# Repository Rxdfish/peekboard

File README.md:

Repo for peekboard a small desk display, showing some infos about this and that 

# peekboard

This is a practical and useful table display. Its meant to create a info dashboard to display all sorts of stuff. It could show your notifications and files or simply the time and date. 
This project is WOP so expect changes and updates in future!

# What is this

Peekboard is another project, made for the [Half life](https://halflife.hackclub.com) by Hackclub YSWS program. The motivation for this project was to build a display. Since bigger displays cost more money, this 4" TFT screen was everything that fit into the tight budget. Even though the limitations, I think it worked out quite nicely and im really excited to test it out myself.

The Board features as probably suspected a Microcontroller, display, some buttons and rotary encoders and a USB-C receptacle. The whole board fits into one hand!

# Project status

The project is as already said a WOP and there will come more polished versions of the project. Also in work is an enclosure for the display, that can be 3D printed.  

# Detailed description

More detailed description coming soon. For now refer to the images and the #What is this chapter.
-features
-controls
-menus
-settings

# Motivation

There was no deeper motivation than to differentiate my skills more and test some new components. Half life gave the display topic and I went with it happily.

# Project journaling

Via the [Half life](https://halflife.hackclub.com) by Hackclub programm, several Journal entries have been made either in timelaps form or as written entry to track the project, that describe the project further. Right now they arent public, but either they will, or some screenshots will be added to the repo

# Assembly

The assembly should be quite beginnerfriendly. All components can be handsoldered onto a PCB that can be ordered by a manufacturer like [JLPCB](https://jlcpcb.com/). Maybe a video tutorial will be added later (if the repo is seen, but prob. not). 

# Schematic and components

The board is powered by the ESP32-S3-WROOM-1-N16R8. It provides some power and data for flashing and firmware. The board also features another USB-C receptacle for main power of the TFT screen. This display is a 4" st7796 SPI TFT 480x320 screen, that is fairly big for its price. For navigation, setup and use, there are several buttons and rotary encoders.
If you want to see the schematic in more detail, have a look into the images folder!

# PCB

The PCB is a simple 2 layer PCB with another silkscreen layer for cosmetic and organisational purposes. The board also has a standart GND pour and features routing on the front and backside.

closeup

# Firmware

There is no official firmware yet but there is some test software inside the repo and the basic firmware for the screen. More will follow soon.

**!Short disclaimer for half life!**

There is no finished .ino or .py file in the repo but there are some test script in other formats for the screen. The actual finished firmware will be created in the build week.

# BOM
There are two BOM files inside the repo. One is the entire parts list with all passives and main components. Its stored in BOM2. The other is the list below or saved in [BOM.csv](BOM.csv). THis is the funded parts list for the YSWS program by hackclub. If you build the project, you will need BOM2. 

embedded (HL): 
PEEKBOARD – bill of materials
!! The PCB manufacturing was excluded from the list unfortunately because of over budgeting :(
				
| Part | Qty | Unit-Price | total | Shop | Link |
| --- | --- | --- | --- | --- | --- |
| 4" st7796 SPI TFT 480x320 | 1 | $20.93 | $20.93 | AliExpress | [Link](https://de.aliexpress.com/item/1005007609041421.html?spm=a2g0o.cart.0.0.502038dawLfZEM&mp=1&gatewayAdapt=glo2deu) |
| USBLC6-2SC6 | 1 | $1.72 | $1.72 | AliExpress | [Link](https://de.aliexpress.com/item/1005007348100430.html?spm=a2g0o.cart.0.0.502038dawLfZEM&mp=1&gatewayAdapt=glo2deu) |
| AP1221K-3.3 TRG1 | 1 | $2.36 | $2.36 | AliExpress | [Link](https://de.aliexpress.com/item/1005005807114594.html?spm=a2g0o.cart.0.0.502038daN9aA73&mp=1&gatewayAdapt=glo2deu) |
| AO3401A | 1 | $2.09 | $2.09 | AliExpress | [Link](https://www.aliexpress.com/item/1005006220143887.html?spm=a2g0o.cart.0.0.44c538daCDAQGZ&mp=1) |
| Alps EC11E155244G1 | 1 | $1.27 | $1.27 | AliExpress | [Link](https://de.aliexpress.com/item/1005007644083514.html?spm=a2g0o.cart.0.0.502038daN9aA73&mp=1&gatewayAdapt=glo2deu) |
| 1206 PTC self recovery fuse 0.75A | 1 | $1.93 | $1.93 | AliExpress | [Link](https://de.aliexpress.com/item/1005005750933997.html?spm=a2g0o.cart.0.0.44c538daCDAQGZ&mp=1&gatewayAdapt=glo2deu) |
| (PCB manufacturing) | 5 | $8.6 | $8.6 | JLPCB | [Link](https://cart.jlcpcb.com/de/quote?stencilLayer=2&stencilWidth=100&stencilLength=100&stencilCounts=5&plateType=1&spm=Jlcpcb.Homepage.1010) |
| **Total** | **$28.93** | | Shipping: free | (Shipping for PCB: $8.99) | |

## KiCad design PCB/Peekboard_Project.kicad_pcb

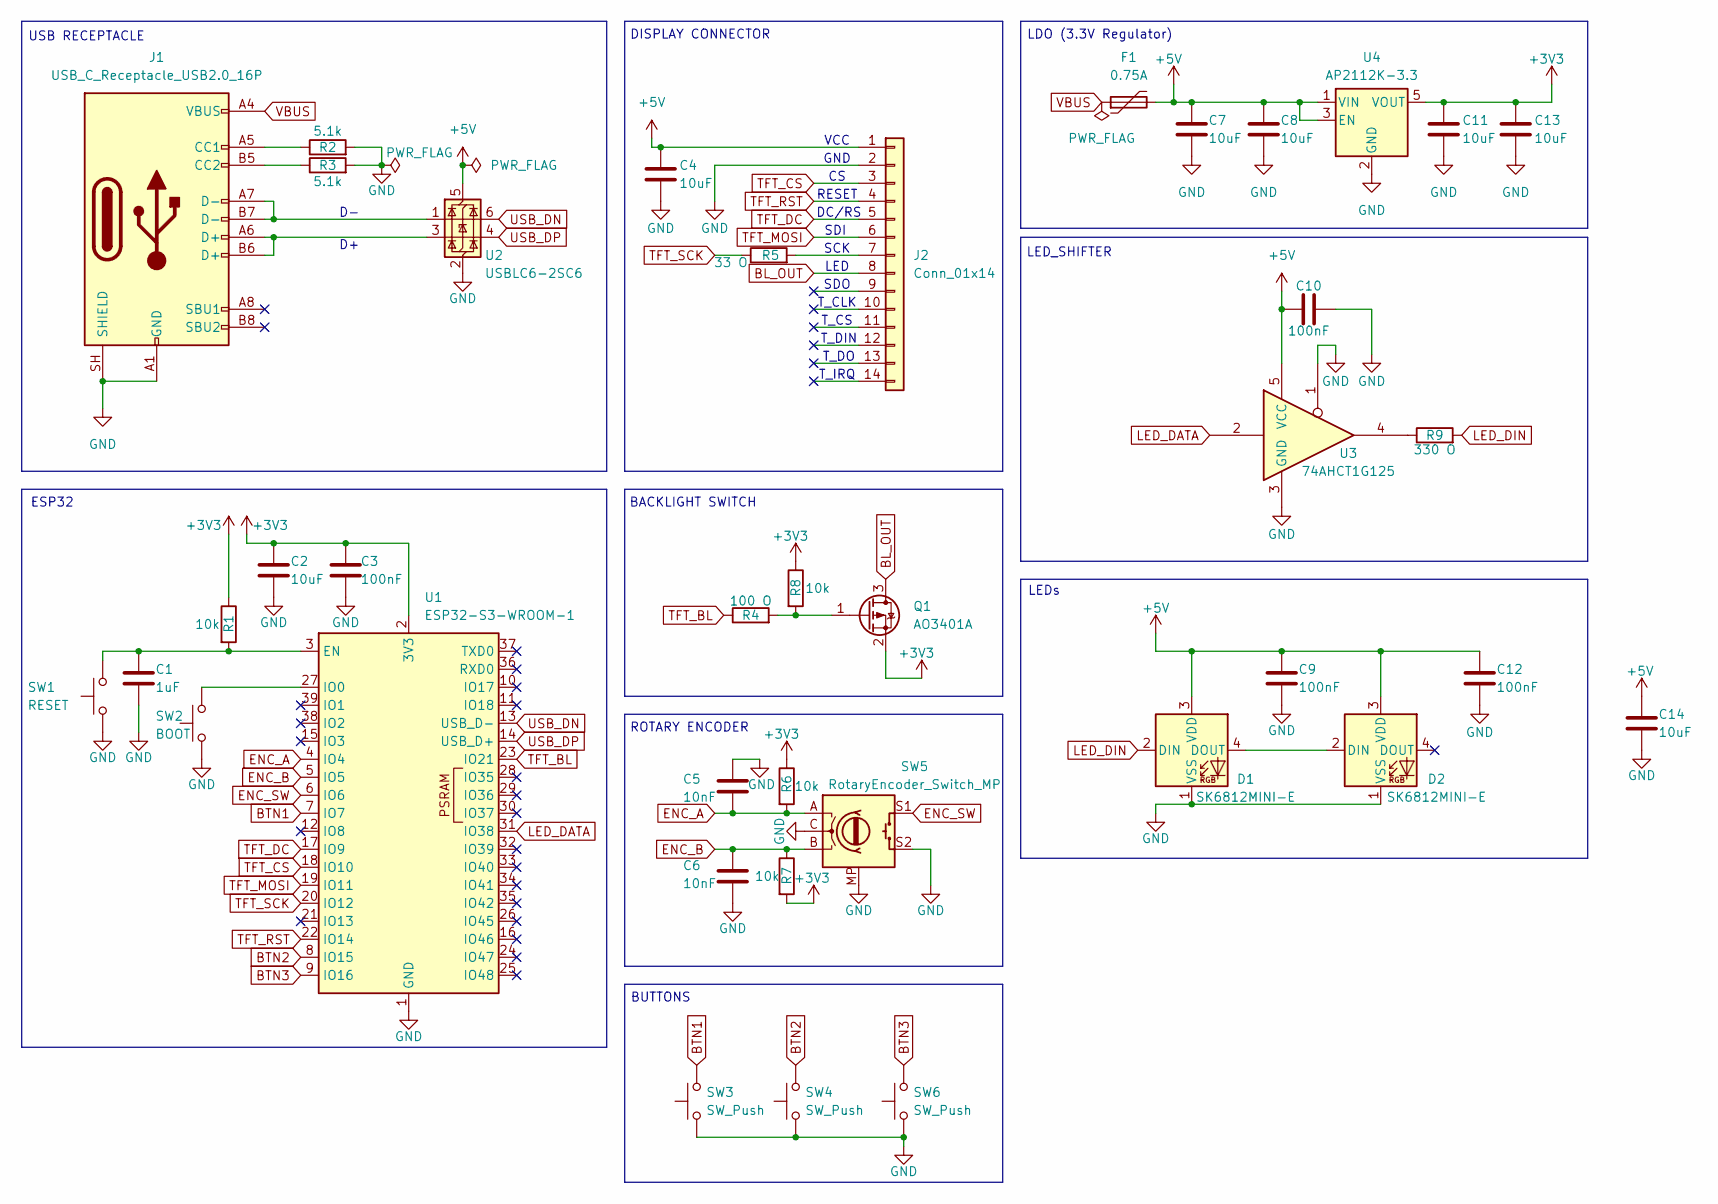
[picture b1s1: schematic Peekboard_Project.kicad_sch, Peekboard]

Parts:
C1: 1uF; C_0805_2012Metric_Pad1.18x1.45mm_HandSolder
C2, C4, C7, C8, C11, C13, C14: 10uF; C_0805_2012Metric_Pad1.18x1.45mm_HandSolder
C3, C9, C10, C12: 100nF; C_0805_2012Metric_Pad1.18x1.45mm_HandSolder
C5, C6: 10nF; C_0805_2012Metric_Pad1.18x1.45mm_HandSolder
D1, D2: SK6812MINI-E; LED_SK6812MINI-E_3.2x2.8mm_P1.5mm_ReverseMount
F1: 0.75A; Fuse_1206_3216Metric_Pad1.42x1.75mm_HandSolder
J1: USB_C_Receptacle_USB2.0_16P; USB_C_Receptacle_HRO_TYPE-C-31-M-12
J2: Conn_01x14; MSP4030_Module
Q1: AO3401A; SOT-23
R1, R6, R7, R8: 10k; R_0805_2012Metric_Pad1.20x1.40mm_HandSolder
R2, R3: 5.1k; R_0805_2012Metric_Pad1.20x1.40mm_HandSolder
R4: 100 O; R_0805_2012Metric_Pad1.20x1.40mm_HandSolder
R5: 33 O; R_0805_2012Metric_Pad1.20x1.40mm_HandSolder
R9: 330 O; R_0805_2012Metric_Pad1.20x1.40mm_HandSolder
SW1: RESET; SW_PUSH_6mm
SW2: BOOT; SW_PUSH_6mm
SW3, SW4, SW6: SW_Push; SW_PUSH_6mm
SW5: RotaryEncoder_Switch_MP; RotaryEncoder_Alps_EC11E-Switch_Vertical_H20mm
U1: ESP32-S3-WROOM-1
U2: USBLC6-2SC6; SOT-23-6_Handsoldering
U3: 74AHCT1G125; SOT-23-5_HandSoldering
U4: AP2112K-3.3; SOT-23-5_HandSoldering

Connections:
+3V3: C2.1, C3.1, C11.1, C13.1, Q1.2 (S), R1.1, R6.1, R7.2, R8.1, U1.2 (3V3), U4.5 (VOUT)
+5V: C4.1, C7.1, C8.1, C9.1, C10.1, C12.1, C14.1, D1.3 (VDD), D2.3 (VDD), F1.2, J2.1, U2.5 (VBUS), U3.5 (VCC), U4.1 (VIN), U4.3 (EN)
BL_OUT: J2.8, Q1.3 (D)
BTN1: SW3.2, U1.7 (IO7)
BTN2: SW4.2, U1.8 (IO15)
BTN3: SW6.2, U1.9 (IO16)
ENC_A: C5.2, R6.2, SW5.A, U1.4 (IO4)
ENC_B: C6.1, R7.1, SW5.B, U1.5 (IO5)
ENC_SW: SW5.S1, U1.6 (IO6)
GND: C1.2, C2.2, C3.2, C4.2, C5.1, C6.2, C7.2, C8.2, C9.2, C10.2, C11.2, C12.2, C13.2, C14.2, D1.1 (VSS), D2.1 (VSS), J1.A1 (GND), J1.A12 (GND), J1.B1 (GND), J1.B12 (GND), J1.SH (SHIELD), J2.2, R2.2, R3.2, SW1.1, SW2.1, SW3.1, SW4.1, SW5.C, SW5.MP, SW5.S2, SW6.1, U1.1 (GND), U1.40 (GND), U1.41 (GND), U2.2 (GND), U3.1, U3.3 (GND), U4.2 (GND)
LED_DATA: U1.31 (IO38), U3.2
LED_DIN: D1.2 (DIN), R9.2
unnamed: D1.4 (DOUT), D2.2 (DIN)
unnamed: J1.A5 (CC1), R2.1
unnamed: J1.B5 (CC2), R3.1
unnamed: J1.A6 (D+), J1.B6 (D+), U2.3 (I/O2)
unnamed: J1.A7 (D-), J1.B7 (D-), U2.1 (I/O1)
unnamed: J2.7, R5.2
unnamed: Q1.1 (G), R4.2, R8.2
unnamed: R9.1, U3.4
unnamed: C1.1, R1.2, SW1.2, U1.3 (EN)
unnamed: SW2.2, U1.27 (IO0)
TFT_BL: R4.1, U1.23 (IO21)
TFT_CS: J2.3, U1.18 (IO10)
TFT_DC: J2.5, U1.17 (IO9)
TFT_MOSI: J2.6, U1.19 (IO11)
TFT_RST: J2.4, U1.22 (IO14)
TFT_SCK: R5.1, U1.20 (IO12)
USB_DN: U1.13 (USB_D-), U2.6 (I/O1)
USB_DP: U1.14 (USB_D+), U2.4 (I/O2)
VBUS: F1.1, J1.A4 (VBUS), J1.A9 (VBUS), J1.B4 (VBUS), J1.B9 (VBUS)

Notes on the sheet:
LDO (3.3V Regulator)
SCK
T_DO
SDI
ROTARY ENCODER
VCC
T_CS
USB RECEPTACLE
T_IRQ
LED_SHIFTER
ESP32
LEDs
LED
GND
T_DIN
DC/RS
DISPLAY CONNECTOR
SDO
BUTTONS
BACKLIGHT SWITCH
T_CLK
RESET

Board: 2 copper layers, 39 parts (11 on the bottom side), 31 nets, no tracks yet.
